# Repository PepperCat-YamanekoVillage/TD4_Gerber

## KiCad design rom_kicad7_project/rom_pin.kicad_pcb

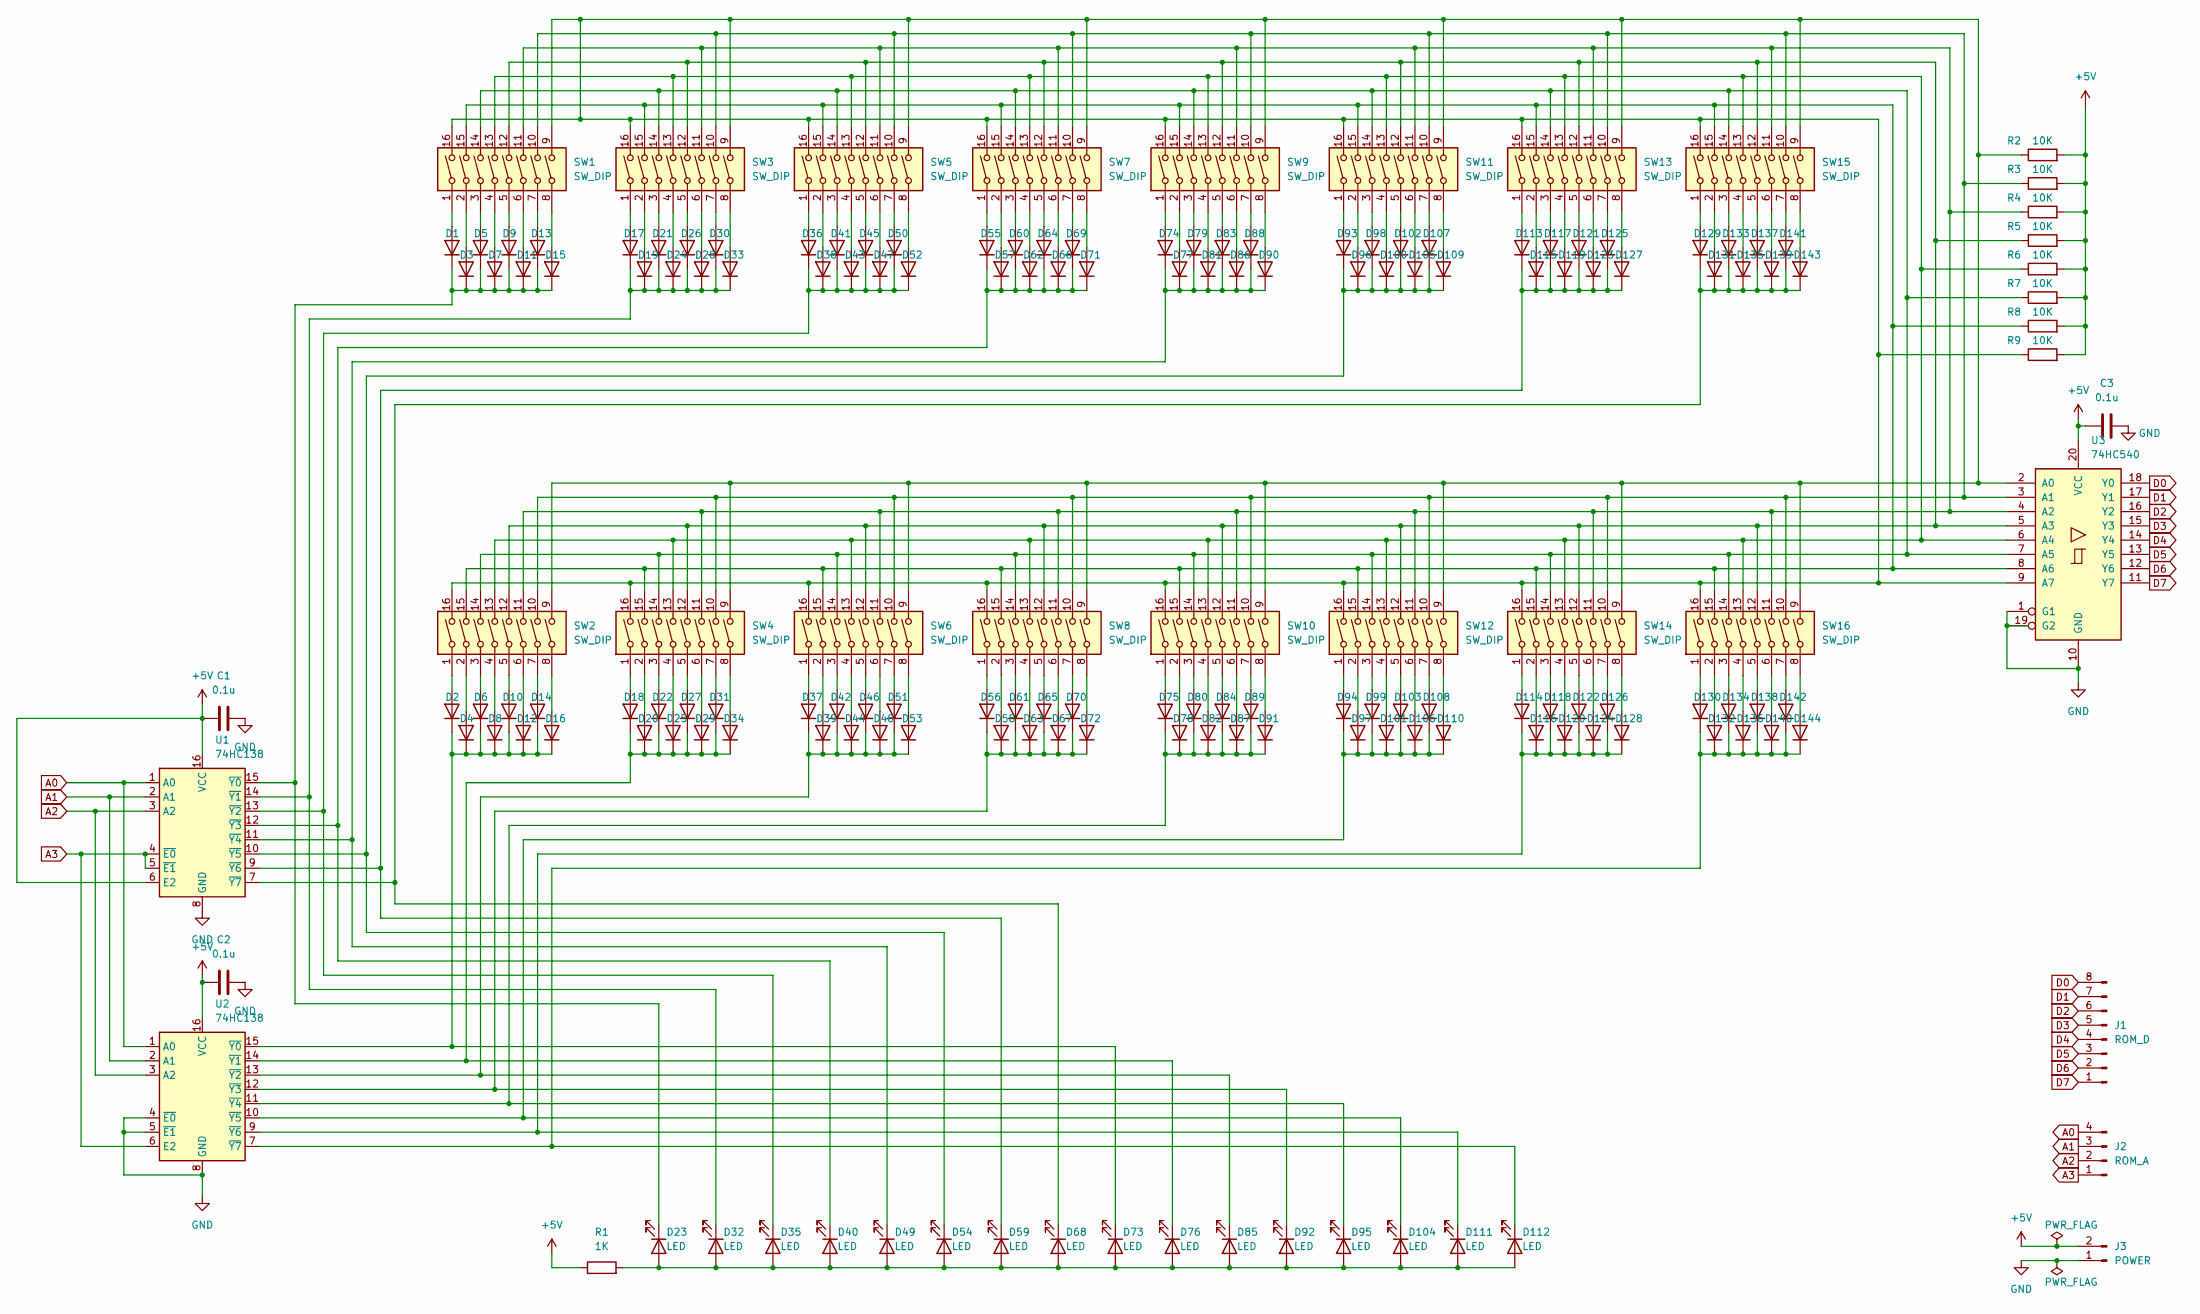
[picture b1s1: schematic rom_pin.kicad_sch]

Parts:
C1, C2, C3: 0.1u; C_0402_1005Metric; LCSC C1525
D1, D2, D3, D4, D5, D6, D7, D8, D9, D10, D11, D12, D13, D14, D15, D16, D17, D18, D19, D20, D21, D22, D24, D25, D26, D27, D28, D29, D30, D31, D33, D34, D36, D37, D38, D39, D41, D42, D43, D44, D45, D46, D47, D48, D50, D51, D52, D53, D55, D56, D57, D58, D60, D61, D62, D63, D64, D65, D66, D67, D69, D70, D71, D72, D74, D75, D77, D78, D79, D80, D81, D82, D83, D84, D86, D87, D88, D89, D90, D91, D93, D94, D96, D97, D98, D99, D100, D101, D102, D103, D105, D106, D107, D108, D109, D110, D113, D114, D115, D116, D117, D118, D119, D120, D121, D122, D123, D124, D125, D126, D127, D128, D129, D130, D131, D132, D133, D134, D135, D136, D137, D138, D139, D140, D141, D142, D143, D144: D; D_SOD-323; LCSC C2128
D23, D32, D35, D40, D49, D54, D59, D68, D73, D76, D85, D92, D95, D104, D111, D112: LED; LED_0603_1608Metric; LCSC C2286
J1: ROM_D; PinHeader_1x08_P2.54mm_Vertical; LCSC x
J2: ROM_A; PinHeader_1x04_P2.54mm_Vertical; LCSC x
J3: POWER; PinHeader_1x02_P2.54mm_Vertical; LCSC x
R1: 1K; R_0603_1608Metric; LCSC C21190
R2, R3, R4, R5, R6, R7, R8, R9: 10K; R_0603_1608Metric; LCSC C25804
SW1, SW2, SW3, SW4, SW5, SW6, SW7, SW8, SW9, SW10, SW11, SW12, SW13, SW14, SW15, SW16: SW_DIP; SW_DIP_SPSTx08_Slide_9.78x22.5mm_W7.62mm_P2.54mm; LCSC x
U1, U2: 74HC138; DIP-16_W7.62mm_Socket; LCSC x
U3: 74HC540; DIP-20_W7.62mm_Socket; LCSC x

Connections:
+5V: C1.1, C2.1, C3.1, J3.2, R1.1, R2.2, R3.2, R4.2, R5.2, R6.2, R7.2, R8.2, R9.2, U1.6 (E2), U1.16 (VCC), U2.16 (VCC), U3.20 (VCC)
A0: J2.4, U1.1 (A0), U2.1 (A0)
A1: J2.3, U1.2 (A1), U2.2 (A1)
A2: J2.2, U1.3 (A2), U2.3 (A2)
A3: J2.1, U1.4 (~E0), U1.5 (~E1), U2.6 (E2)
D0: J1.8, U3.18 (Y0)
D1: J1.7, U3.17 (Y1)
D2: J1.6, U3.16 (Y2)
D3: J1.5, U3.15 (Y3)
D4: J1.4, U3.14 (Y4)
D5: J1.3, U3.13 (Y5)
D6: J1.2, U3.12 (Y6)
D7: J1.1, U3.11 (Y7)
GND: C1.2, C2.2, C3.2, J3.1, U1.8 (GND), U2.4 (~E0), U2.5 (~E1), U2.8 (GND), U3.1 (G1), U3.10 (GND), U3.19 (G2)
unnamed: D1.2 (A), SW1.1
unnamed: D1.1 (K), D3.1 (K), D5.1 (K), D7.1 (K), D9.1 (K), D11.1 (K), D13.1 (K), D15.1 (K), D23.1 (K), U1.15 (~Y0)
unnamed: D2.2 (A), SW2.1
unnamed: D3.2 (A), SW1.2
unnamed: D4.2 (A), SW2.2
unnamed: D5.2 (A), SW1.3
unnamed: D6.2 (A), SW2.3
unnamed: D7.2 (A), SW1.4
unnamed: D8.2 (A), SW2.4
unnamed: D9.2 (A), SW1.5
unnamed: D10.2 (A), SW2.5
unnamed: D2.1 (K), D4.1 (K), D6.1 (K), D8.1 (K), D10.1 (K), D12.1 (K), D14.1 (K), D16.1 (K), D73.1 (K), U2.15 (~Y0)
unnamed: D11.2 (A), SW1.6
unnamed: D12.2 (A), SW2.6
unnamed: D13.2 (A), SW1.7
unnamed: D14.2 (A), SW2.7
unnamed: D15.2 (A), SW1.8
unnamed: D16.2 (A), SW2.8
unnamed: D17.2 (A), SW3.1
unnamed: D17.1 (K), D19.1 (K), D21.1 (K), D24.1 (K), D26.1 (K), D28.1 (K), D30.1 (K), D32.1 (K), D33.1 (K), U1.14 (~Y1)
unnamed: D18.2 (A), SW4.1
unnamed: D18.1 (K), D20.1 (K), D22.1 (K), D25.1 (K), D27.1 (K), D29.1 (K), D31.1 (K), D34.1 (K), D76.1 (K), U2.14 (~Y1)
unnamed: D19.2 (A), SW3.2
unnamed: D20.2 (A), SW4.2
unnamed: D21.2 (A), SW3.3
unnamed: D22.2 (A), SW4.3
unnamed: D24.2 (A), SW3.4
unnamed: D25.2 (A), SW4.4
unnamed: D26.2 (A), SW3.5
unnamed: D27.2 (A), SW4.5
unnamed: D28.2 (A), SW3.6
unnamed: D29.2 (A), SW4.6
unnamed: D30.2 (A), SW3.7
unnamed: D31.2 (A), SW4.7
unnamed: D33.2 (A), SW3.8
unnamed: D34.2 (A), SW4.8
unnamed: D35.1 (K), D36.1 (K), D38.1 (K), D41.1 (K), D43.1 (K), D45.1 (K), D47.1 (K), D50.1 (K), D52.1 (K), U1.13 (~Y2)
unnamed: D36.2 (A), SW5.1
unnamed: D37.2 (A), SW6.1
unnamed: D37.1 (K), D39.1 (K), D42.1 (K), D44.1 (K), D46.1 (K), D48.1 (K), D51.1 (K), D53.1 (K), D85.1 (K), U2.13 (~Y2)
unnamed: D38.2 (A), SW5.2
unnamed: D39.2 (A), SW6.2
unnamed: D40.1 (K), D55.1 (K), D57.1 (K), D60.1 (K), D62.1 (K), D64.1 (K), D66.1 (K), D69.1 (K), D71.1 (K), U1.12 (~Y3)
unnamed: D41.2 (A), SW5.3
unnamed: D42.2 (A), SW6.3
unnamed: D43.2 (A), SW5.4
unnamed: D44.2 (A), SW6.4
unnamed: D45.2 (A), SW5.5
unnamed: D46.2 (A), SW6.5
unnamed: D47.2 (A), SW5.6
unnamed: D48.2 (A), SW6.6
unnamed: D49.1 (K), D74.1 (K), D77.1 (K), D79.1 (K), D81.1 (K), D83.1 (K), D86.1 (K), D88.1 (K), D90.1 (K), U1.11 (~Y4)
unnamed: D50.2 (A), SW5.7
unnamed: D51.2 (A), SW6.7
unnamed: D52.2 (A), SW5.8
unnamed: D53.2 (A), SW6.8
unnamed: D55.2 (A), SW7.1
unnamed: D56.2 (A), SW8.1
unnamed: D56.1 (K), D58.1 (K), D61.1 (K), D63.1 (K), D65.1 (K), D67.1 (K), D70.1 (K), D72.1 (K), D92.1 (K), U2.12 (~Y3)
unnamed: D57.2 (A), SW7.2
unnamed: D58.2 (A), SW8.2
unnamed: D60.2 (A), SW7.3
unnamed: D61.2 (A), SW8.3
unnamed: D62.2 (A), SW7.4
unnamed: D63.2 (A), SW8.4
unnamed: D64.2 (A), SW7.5
unnamed: D65.2 (A), SW8.5
unnamed: D66.2 (A), SW7.6
unnamed: D67.2 (A), SW8.6
unnamed: D69.2 (A), SW7.7
unnamed: D70.2 (A), SW8.7
unnamed: D71.2 (A), SW7.8
unnamed: D72.2 (A), SW8.8
unnamed: D74.2 (A), SW9.1
unnamed: D75.2 (A), SW10.1
unnamed: D75.1 (K), D78.1 (K), D80.1 (K), D82.1 (K), D84.1 (K), D87.1 (K), D89.1 (K), D91.1 (K), D95.1 (K), U2.11 (~Y4)
unnamed: D77.2 (A), SW9.2
unnamed: D78.2 (A), SW10.2
unnamed: D79.2 (A), SW9.3
unnamed: D80.2 (A), SW10.3
unnamed: D81.2 (A), SW9.4
unnamed: D82.2 (A), SW10.4
unnamed: D83.2 (A), SW9.5
unnamed: D84.2 (A), SW10.5
unnamed: D86.2 (A), SW9.6
unnamed: D87.2 (A), SW10.6
unnamed: D88.2 (A), SW9.7
unnamed: D89.2 (A), SW10.7
unnamed: D90.2 (A), SW9.8
unnamed: D91.2 (A), SW10.8
unnamed: D93.2 (A), SW11.1
unnamed: D94.2 (A), SW12.1
unnamed: D96.2 (A), SW11.2
unnamed: D97.2 (A), SW12.2
unnamed: D98.2 (A), SW11.3
unnamed: D99.2 (A), SW12.3
unnamed: D100.2 (A), SW11.4
unnamed: D54.1 (K), D93.1 (K), D96.1 (K), D98.1 (K), D100.1 (K), D102.1 (K), D105.1 (K), D107.1 (K), D109.1 (K), U1.10 (~Y5)
unnamed: D101.2 (A), SW12.4
unnamed: D94.1 (K), D97.1 (K), D99.1 (K), D101.1 (K), D103.1 (K), D104.1 (K), D106.1 (K), D108.1 (K), D110.1 (K), U2.10 (~Y5)
unnamed: D102.2 (A), SW11.5
unnamed: D103.2 (A), SW12.5
unnamed: D23.2 (A), D32.2 (A), D35.2 (A), D40.2 (A), D49.2 (A), D54.2 (A), D59.2 (A), D68.2 (A), D73.2 (A), D76.2 (A), D85.2 (A), D92.2 (A), D95.2 (A), D104.2 (A), D111.2 (A), D112.2 (A), R1.2
unnamed: D105.2 (A), SW11.6
unnamed: D106.2 (A), SW12.6
unnamed: D107.2 (A), SW11.7
unnamed: D108.2 (A), SW12.7
unnamed: D109.2 (A), SW11.8
unnamed: D110.2 (A), SW12.8
unnamed: D111.1 (K), D114.1 (K), D116.1 (K), D118.1 (K), D120.1 (K), D122.1 (K), D124.1 (K), D126.1 (K), D128.1 (K), U2.9 (~Y6)
unnamed: D112.1 (K), D130.1 (K), D132.1 (K), D134.1 (K), D136.1 (K), D138.1 (K), D140.1 (K), D142.1 (K), D144.1 (K), U2.7 (~Y7)
unnamed: D113.2 (A), SW13.1
unnamed: D59.1 (K), D113.1 (K), D115.1 (K), D117.1 (K), D119.1 (K), D121.1 (K), D123.1 (K), D125.1 (K), D127.1 (K), U1.9 (~Y6)
unnamed: D114.2 (A), SW14.1
unnamed: D115.2 (A), SW13.2
unnamed: D116.2 (A), SW14.2
unnamed: D117.2 (A), SW13.3
unnamed: D118.2 (A), SW14.3
unnamed: D119.2 (A), SW13.4
unnamed: D120.2 (A), SW14.4
unnamed: D121.2 (A), SW13.5
unnamed: D122.2 (A), SW14.5
unnamed: D123.2 (A), SW13.6
unnamed: D124.2 (A), SW14.6
unnamed: D125.2 (A), SW13.7
unnamed: D126.2 (A), SW14.7
unnamed: D127.2 (A), SW13.8
unnamed: D128.2 (A), SW14.8
unnamed: D129.2 (A), SW15.1
unnamed: D68.1 (K), D129.1 (K), D131.1 (K), D133.1 (K), D135.1 (K), D137.1 (K), D139.1 (K), D141.1 (K), D143.1 (K), U1.7 (~Y7)
unnamed: D130.2 (A), SW16.1
unnamed: D131.2 (A), SW15.2
unnamed: D132.2 (A), SW16.2
unnamed: D133.2 (A), SW15.3
unnamed: D134.2 (A), SW16.3
unnamed: D135.2 (A), SW15.4
unnamed: D136.2 (A), SW16.4
unnamed: D137.2 (A), SW15.5
unnamed: D138.2 (A), SW16.5
unnamed: D139.2 (A), SW15.6
unnamed: D140.2 (A), SW16.6
unnamed: D141.2 (A), SW15.7
unnamed: D142.2 (A), SW16.7
unnamed: D143.2 (A), SW15.8
unnamed: D144.2 (A), SW16.8
unnamed: R3.1, SW1.10, SW2.10, SW3.10, SW4.10, SW5.10, SW6.10, SW7.10, SW8.10, SW9.10, SW10.10, SW11.10, SW12.10, SW13.10, SW14.10, SW15.10, SW16.10, U3.3 (A1)
unnamed: R4.1, SW1.11, SW2.11, SW3.11, SW4.11, SW5.11, SW6.11, SW7.11, SW8.11, SW9.11, SW10.11, SW11.11, SW12.11, SW13.11, SW14.11, SW15.11, SW16.11, U3.4 (A2)
unnamed: R5.1, SW1.12, SW2.12, SW3.12, SW4.12, SW5.12, SW6.12, SW7.12, SW8.12, SW9.12, SW10.12, SW11.12, SW12.12, SW13.12, SW14.12, SW15.12, SW16.12, U3.5 (A3)
unnamed: R6.1, SW1.13, SW2.13, SW3.13, SW4.13, SW5.13, SW6.13, SW7.13, SW8.13, SW9.13, SW10.13, SW11.13, SW12.13, SW13.13, SW14.13, SW15.13, SW16.13, U3.6 (A4)
unnamed: R7.1, SW1.14, SW2.14, SW3.14, SW4.14, SW5.14, SW6.14, SW7.14, SW8.14, SW9.14, SW10.14, SW11.14, SW12.14, SW13.14, SW14.14, SW15.14, SW16.14, U3.7 (A5)
unnamed: R8.1, SW1.15, SW2.15, SW3.15, SW4.15, SW5.15, SW6.15, SW7.15, SW8.15, SW9.15, SW10.15, SW11.15, SW12.15, SW13.15, SW14.15, SW15.15, SW16.15, U3.8 (A6)

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
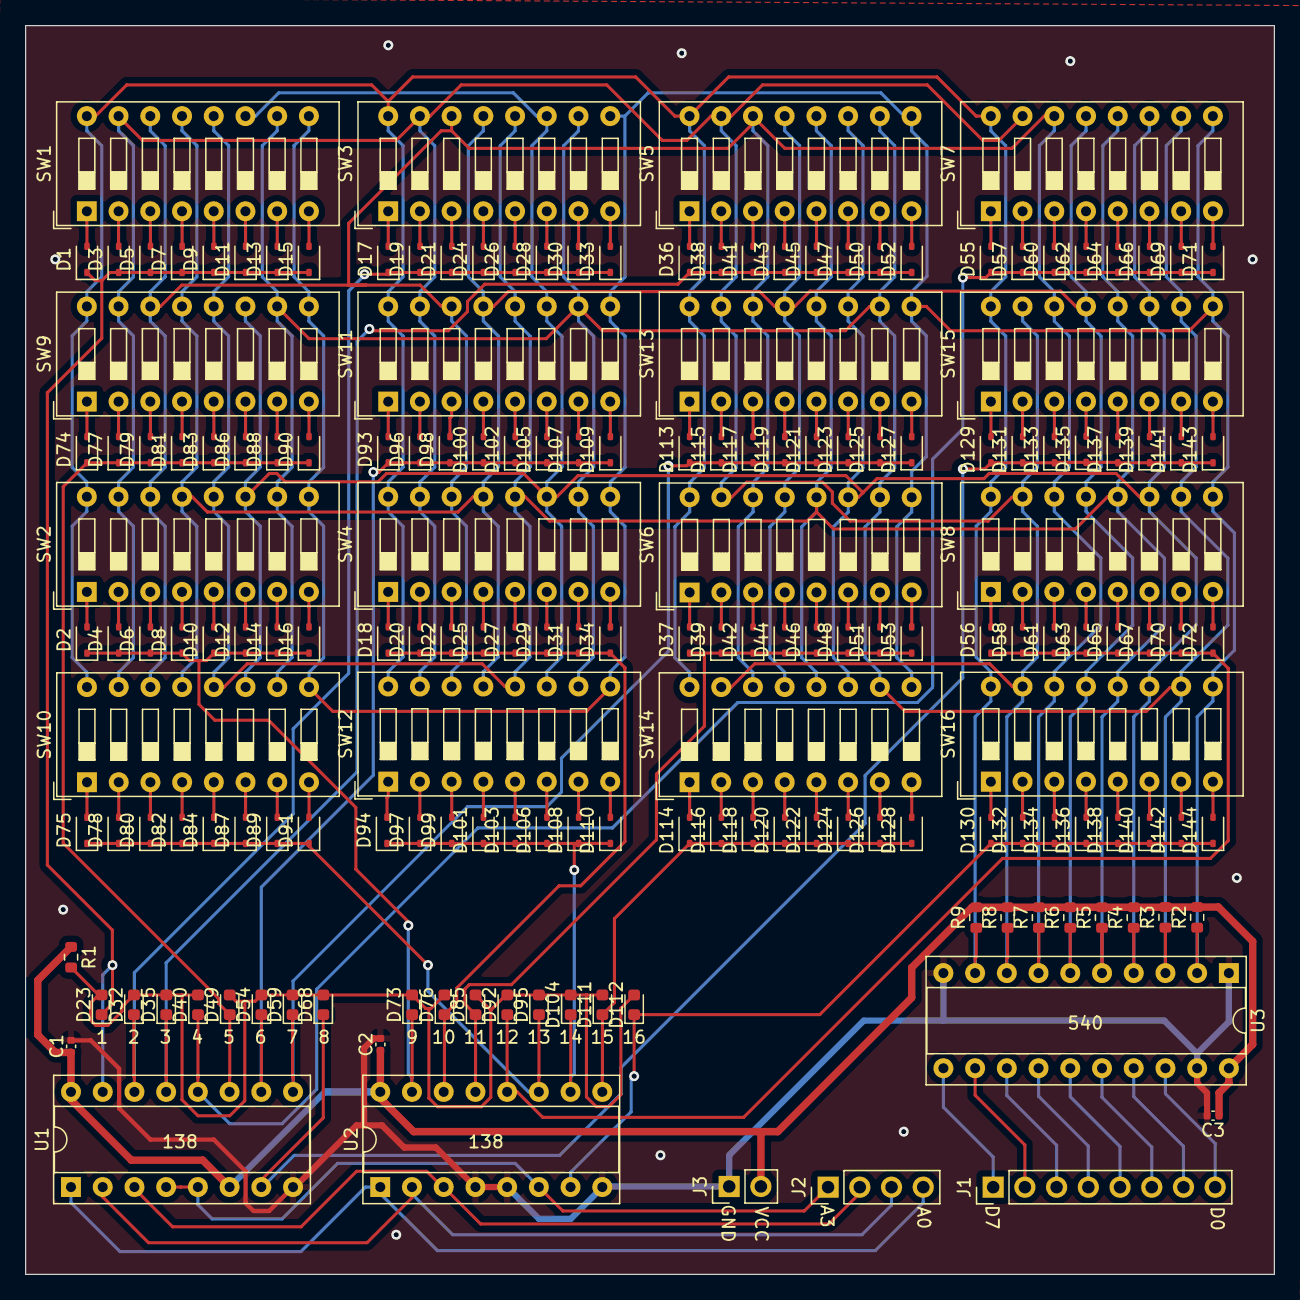
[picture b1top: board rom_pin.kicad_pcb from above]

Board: 2 copper layers, 100.0 x 100.0 mm, 178 parts (0 on the bottom side), 167 nets.

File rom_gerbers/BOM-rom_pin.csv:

Comment,Designator,Footprint,LCSC
0.1u,"C1,C2,C3",C_0402_1005Metric,C1525
1K,R1,R_0603_1608Metric,C21190
D,"D1,D10,D100,D101,D102,D103,D105,D106,D107,D108,D109,D11,D110,D113,D114,D115,D116,D117,D118,D119,D12,D120,D121,D122,D123,D124,D125,D126,D127,D128,D129,D13,D130,D131,D132,D133,D134,D135,D136,D137,D138,D139,D14,D140,D141,D142,D143,D144,D15,D16,D17,D18,D19,D2,D20,D21,D22,D24,D25,D26,D27,D28,D29,D3,D30,D31,D33,D34,D36,D37,D38,D39,D4,D41,D42,D43,D44,D45,D46,D47,D48,D5,D50,D51,D52,D53,D55,D56,D57,D58,D6,D60,D61,D62,D63,D64,D65,D66,D67,D69,D7,D70,D71,D72,D74,D75,D77,D78,D79,D8,D80,D81,D82,D83,D84,D86,D87,D88,D89,D9,D90,D91,D93,D94,D96,D97,D98,D99",D_SOD-323,C2128
LED,"D104,D111,D112,D23,D32,D35,D40,D49,D54,D59,D68,D73,D76,D85,D92,D95",LED_0603_1608Metric,C2286
10K,"R2,R3,R4,R5,R6,R7,R8,R9",R_0603_1608Metric,C25804
SW_DIP,SW7,SW_DIP_SPSTx08_Slide_9.78x22.5mm_W7.62mm_P2.54mm,
ROM_D,J1,PinHeader_1x08_P2.54mm_Vertical,
SW_DIP,SW3,SW_DIP_SPSTx08_Slide_9.78x22.5mm_W7.62mm_P2.54mm,
SW_DIP,SW10,SW_DIP_SPSTx08_Slide_9.78x22.5mm_W7.62mm_P2.54mm,
SW_DIP,SW16,SW_DIP_SPSTx08_Slide_9.78x22.5mm_W7.62mm_P2.54mm,
POWER,J3,PinHeader_1x02_P2.54mm_Vertical,
SW_DIP,SW13,SW_DIP_SPSTx08_Slide_9.78x22.5mm_W7.62mm_P2.54mm,
SW_DIP,SW8,SW_DIP_SPSTx08_Slide_9.78x22.5mm_W7.62mm_P2.54mm,
SW_DIP,SW1,SW_DIP_SPSTx08_Slide_9.78x22.5mm_W7.62mm_P2.54mm,
74HC138,U2,DIP-16_W7.62mm_Socket,
SW_DIP,SW4,SW_DIP_SPSTx08_Slide_9.78x22.5mm_W7.62mm_P2.54mm,
SW_DIP,SW6,SW_DIP_SPSTx08_Slide_9.78x22.5mm_W7.62mm_P2.54mm,
SW_DIP,SW2,SW_DIP_SPSTx08_Slide_9.78x22.5mm_W7.62mm_P2.54mm,
74HC138,U1,DIP-16_W7.62mm_Socket,
SW_DIP,SW14,SW_DIP_SPSTx08_Slide_9.78x22.5mm_W7.62mm_P2.54mm,
74HC540,U3,DIP-20_W7.62mm_Socket,
SW_DIP,SW5,SW_DIP_SPSTx08_Slide_9.78x22.5mm_W7.62mm_P2.54mm,
SW_DIP,SW12,SW_DIP_SPSTx08_Slide_9.78x22.5mm_W7.62mm_P2.54mm,
SW_DIP,SW11,SW_DIP_SPSTx08_Slide_9.78x22.5mm_W7.62mm_P2.54mm,
SW_DIP,SW15,SW_DIP_SPSTx08_Slide_9.78x22.5mm_W7.62mm_P2.54mm,
SW_DIP,SW9,SW_DIP_SPSTx08_Slide_9.78x22.5mm_W7.62mm_P2.54mm,
ROM_A,J2,PinHeader_1x04_P2.54mm_Vertical,

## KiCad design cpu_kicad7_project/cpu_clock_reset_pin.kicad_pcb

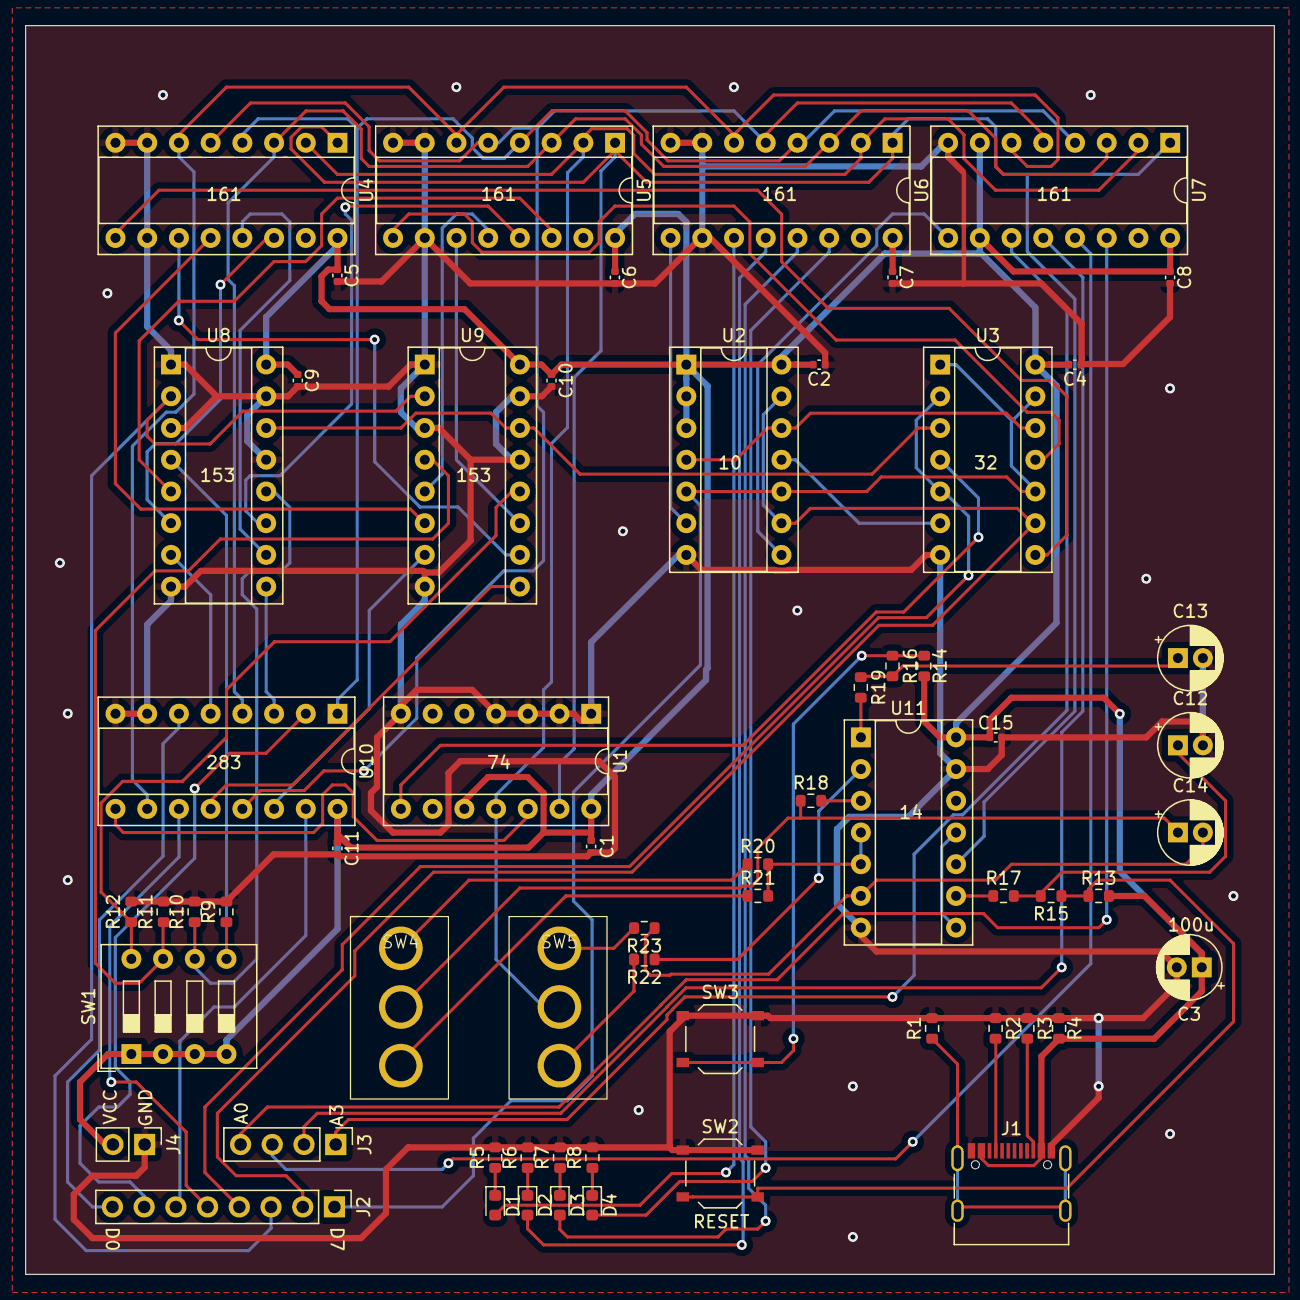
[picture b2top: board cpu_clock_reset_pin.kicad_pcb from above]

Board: 2 copper layers, 100.0 x 100.0 mm, 62 parts (0 on the bottom side), 72 nets.

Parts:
C1, C2, C4, C5, C6, C7, C8, C9, C10, C11, C15: 0.1u; C_0402_1005Metric
C3: 100u 16V; CP_Radial_D5.0mm_P2.00mm
C12, C13, C14: 10uF 16V; CP_Radial_D5.0mm_P2.00mm
D1, D2, D3, D4: LED; LED_0603_1608Metric
J1: USB_C_Receptacle_PowerOnly_6P; USB_C_Receptacle_G-Switch_GT-USB-7010ASV
J2: ROM_D; PinHeader_1x08_P2.54mm_Vertical
J3: ROM_A; PinHeader_1x04_P2.54mm_Vertical
J4: POWER; PinHeader_1x02_P2.54mm_Vertical
R1, R4, R5, R6, R7, R8, R9, R10, R11, R12, R13, R14: 1K; R_0603_1608Metric
R2, R3: 5.1K; R_0603_1608Metric
R15, R17, R18, R19: 100K; R_0603_1608Metric
R16: 10K; R_0603_1608Metric
R20: 3.3K; R_0603_1608Metric
R21: 33K; R_0603_1608Metric
R22, R23: 100; R_0603_1608Metric
SW1: SW_DIP_x04; SW_DIP_SPSTx04_Slide_9.78x12.34mm_W7.62mm_P2.54mm
SW2, SW3: SW_Push; SW_Push_1P1T_XKB_TS-1187A
SW4, SW5: SW_SPDT; toggle_3
U1: 74HC74; DIP-14_W7.62mm_Socket
U2: 74HC10; DIP-14_W7.62mm_Socket
U3: 74HC32; DIP-14_W7.62mm_Socket
U4, U5, U6, U7: 74HC161; DIP-16_W7.62mm_Socket
U8, U9: 74HC153; DIP-16_W7.62mm_Socket
U10: 74HC283; DIP-16_W7.62mm_Socket
U11: 74HC14; DIP-14_W7.62mm_Socket

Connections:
+5V: C1.2, C2.2, C3.1, C4.2, C5.1, C6.1, C7.1, C8.1, C9.1, C10.1, C11.1, C15.1, J1.A4, J1.A9 (VBUS), J1.B4, J1.B9 (VBUS), J4.2, R4.1, R13.2, R14.1, SW1.1, SW1.2, SW1.3, SW1.4, U1.10 (~S), U1.14 (VCC), U2.1, U2.2, U2.3, U2.14 (VCC), U3.14 (VCC), U4.16 (VCC), U5.16 (VCC), U6.16 (VCC), U7.7 (ENP), U7.10 (ENT), U7.16 (VCC), U8.16 (VCC), U9.16 (VCC), U10.16 (VCC), U11.14 (VCC)
A0: J3.4, U7.14 (Q0)
A1: J3.3, U7.13 (Q1)
A2: J3.2, U7.12 (Q2)
A3: J3.1, U7.11 (Q3)
CLOCK: SW5.2 (B), U1.11 (C), U4.2 (CK), U5.2 (CK), U6.2 (CK), U7.2 (CK)
D0: J2.8, U10.6 (B1)
D1: J2.7, U10.2 (B2)
D2: J2.6, U10.15 (B3)
D3: J2.5, U10.11 (B4)
D4: J2.4, U3.2, U3.5
D5: J2.3, U8.2 (S1), U9.2 (S1)
D6: J2.2, U2.9, U2.13, U3.9
D7: J2.1, U2.5, U2.10, U3.1, U3.10, U3.13
GND: C1.1, C2.1, C3.2, C4.1, C5.2, C6.2, C7.2, C8.2, C9.2, C10.2, C11.2, C12.2, C13.2, C15.2, J1.A1, J1.A12 (GND), J1.B1, J1.B12 (GND), J4.1, R1.2, R2.1, R3.1, R4.2, R5.2, R6.2, R7.2, R8.2, R9.2, R10.2, R11.2, R12.2, SW2.1, SW3.1, U1.1 (~R), U1.2 (D), U1.3 (C), U1.4 (~S), U1.7 (GND), U2.7 (GND), U3.7 (GND), U4.7 (ENP), U4.8 (GND), U4.10 (ENT), U5.7 (ENP), U5.8 (GND), U5.10 (ENT), U6.7 (ENP), U6.8 (GND), U6.10 (ENT), U7.8 (GND), U8.1 (Ea), U8.3 (13a), U8.8 (GND), U8.13 (13b), U8.15 (Eb), U9.1 (Ea), U9.3 (13a), U9.8 (GND), U9.13 (13b), U9.15 (Eb), U10.7 (C0), U10.8 (GND), U11.7 (GND), U11.13
unnamed: C12.1, R15.2, R17.2
unnamed: C13.1, R16.2, R19.1
unnamed: C14.2, R23.1, U11.6
unnamed: D1.2 (A), U6.11 (Q3)
unnamed: D1.1 (K), R5.1
unnamed: D2.2 (A), U6.12 (Q2)
unnamed: D2.1 (K), R6.1
unnamed: D3.2 (A), U6.13 (Q1)
unnamed: D3.1 (K), R7.1
unnamed: D4.2 (A), U6.14 (Q0)
unnamed: D4.1 (K), R8.1
unnamed: J1.A5 (CC1), R2.2
unnamed: J1.B5 (CC2), R3.2
unnamed: J1.S1 (SHIELD), R1.1
unnamed: R13.1, R15.1, SW2.2
unnamed: R14.2, R16.1, SW3.2
unnamed: R17.1, U11.9
unnamed: R18.2, U11.3
unnamed: R19.2, U11.1
unnamed: R20.2, R21.2, U11.4, U11.5
unnamed: R22.1, U11.2
unnamed: R20.1, SW4.1 (A)
unnamed: C14.1, R18.1, SW4.2 (B)
unnamed: R21.1, SW4.3 (C)
unnamed: R23.2, SW5.1 (A)
unnamed: R22.2, SW5.3 (C)
unnamed: U1.8 (~Q), U3.4
unnamed: U2.11, U3.6
unnamed: U2.4, U2.12, U3.12
unnamed: U4.14 (Q0), U8.6 (10a)
unnamed: U4.13 (Q1), U8.10 (10b)
unnamed: U4.12 (Q2), U9.6 (10a)
unnamed: U4.11 (Q3), U9.10 (10b)
unnamed: U3.8, U4.9 (~LOAD)
unnamed: U5.14 (Q0), U8.5 (11a)
unnamed: U5.13 (Q1), U8.11 (11b)
unnamed: U5.12 (Q2), U9.5 (11a)
unnamed: U5.11 (Q3), U9.11 (11b)
unnamed: U3.11, U5.9 (~LOAD)
unnamed: U2.6, U6.9 (~LOAD)
unnamed: U2.8, U7.9 (~LOAD)
unnamed: R9.1, SW1.5, U8.4 (12a)
unnamed: R10.1, SW1.6, U8.12 (12b)
unnamed: U3.3, U8.14 (S0), U9.14 (S0)
unnamed: R11.1, SW1.7, U9.4 (12a)
unnamed: R12.1, SW1.8, U9.12 (12b)
unnamed: U8.7 (Za), U10.5 (A1)
unnamed: U8.9 (Zb), U10.3 (A2)
unnamed: U9.7 (Za), U10.14 (A3)
unnamed: U9.9 (Zb), U10.12 (A4)
unnamed: U1.12 (D), U10.9 (C4)
unnamed: U4.3 (D0), U5.3 (D0), U6.3 (D0), U7.3 (D0), U10.4 (S1)
unnamed: U4.4 (D1), U5.4 (D1), U6.4 (D1), U7.4 (D1), U10.1 (S2)
unnamed: U4.5 (D2), U5.5 (D2), U6.5 (D2), U7.5 (D2), U10.13 (S3)
unnamed: U4.6 (D3), U5.6 (D3), U6.6 (D3), U7.6 (D3), U10.10 (S4)
unnamed: U11.8, U11.11
RESET: U1.13 (~R), U4.1 (~CLR), U5.1 (~CLR), U6.1 (~CLR), U7.1 (~CLR), U11.10

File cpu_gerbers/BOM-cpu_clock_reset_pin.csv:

Comment,Designator,Footprint,LCSC
0.1u,"C1,C10,C11,C15,C2,C4,C5,C6,C7,C8,C9",C_0402_1005Metric,C1525
1K,"R1,R10,R11,R12,R13,R14,R4,R5,R6,R7,R8,R9",R_0603_1608Metric,C21190
100,"R22,R23",R_0603_1608Metric,C22775
LED,"D1,D2,D3,D4",LED_0603_1608Metric,C2286
3.3K,R20,R_0603_1608Metric,C22978
5.1K,"R2,R3",R_0603_1608Metric,C23186
100K,"R15,R17,R18,R19",R_0603_1608Metric,C25803
10K,R16,R_0603_1608Metric,C25804
SW_Push,"SW2,SW3",SW_Push_1P1T_XKB_TS-1187A,C318884
33K,R21,R_0603_1608Metric,C4216
ROM_A,J3,PinHeader_1x04_P2.54mm_Vertical,
ROM_D,J2,PinHeader_1x08_P2.54mm_Vertical,
74HC161,U6,DIP-16_W7.62mm_Socket,
SW_DIP_x04,SW1,SW_DIP_SPSTx04_Slide_9.78x12.34mm_W7.62mm_P2.54mm,
10uF 16V,C13,CP_Radial_D5.0mm_P2.00mm,
USB_C_Receptacle_PowerOnly_6P,J1,USB_C_Receptacle_G-Switch_GT-USB-7010ASV,
10uF 16V,C14,CP_Radial_D5.0mm_P2.00mm,
74HC153,U8,DIP-16_W7.62mm_Socket,
74HC74,U1,DIP-14_W7.62mm_Socket,
74HC161,U7,DIP-16_W7.62mm_Socket,
100u 16V,C3,CP_Radial_D5.0mm_P2.00mm,
74HC10,U2,DIP-14_W7.62mm_Socket,
74HC283,U10,DIP-16_W7.62mm_Socket,
74HC161,U5,DIP-16_W7.62mm_Socket,
74HC14,U11,DIP-14_W7.62mm_Socket,
POWER,J4,PinHeader_1x02_P2.54mm_Vertical,
SW_SPDT,SW4,toggle_3,
10uF 16V,C12,CP_Radial_D5.0mm_P2.00mm,
74HC153,U9,DIP-16_W7.62mm_Socket,
74HC161,U4,DIP-16_W7.62mm_Socket,
74HC32,U3,DIP-14_W7.62mm_Socket,
SW_SPDT,SW5,toggle_3,

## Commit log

2024-07-06 INIT
2024-07-06 ADD circuits' svg
